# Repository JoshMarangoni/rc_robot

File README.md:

# rc_robot

## Project Motivation

NASA's Perseverance rover is a remote controllable rover designed to explore the surface of the Red Planet. The rover primarily uses an ultra-high frequency antenna to communicate with Earth. Data is relayed through Mars satellites back to Earth where engineers can monitor the robot's trajectory and speed.

Although my robot is not designed for Mars, it is designed to explore the outer reaches of my kitchen and living room while I am comfortably relaxing in my bedroom. Instead of orbitting satellites I use my WiFi network and communicate with my robot using http requests. This project is intended to emulate a remote controlled rover such as Perserverence, using my own circuit and software designs.

## Requirements

- Must be able to drive in any direction
- Programmed in C/C+
- Non-arduino based coding envrionment
- Battery powered
- Map "WASD" keys to driving direction

## Bonus features

- All electronics contained on one PCB
- Remote controlled using video feed
- Lag between key presses and robot response < 0.5 s

## Design 1 (MVP) - DONE

- ESP 32 microcontroller programmed in Arduino
- 2 wheels/motors in the rear (RWD)
- 1 wheel/motor in the front
- esp32CAM for video streaming
- Plexiglass chassis

## Design 2 (Feature Complete) - Done

- ESP32 programmed in Expressif IoT Development Framework
- PCB designed in KiCAD and fabricated by JLC PCB
- control terminal for WASD keys written in Python

### Planning (created after completing Design 1)
| Task                                         | Deadline |
|----------------------------------------------|----------|
| get 3D printer working | Nov.19 (Sat) |
| receive MOSFETs | Nov.19 (Sat) |
| get H-bridges working | Nov.20 (Sun) |
| test singular power source with capacitor | Nov.20 (Sun) |
| finish PCB design and send order for fab | Nov.27 (Sun) |
| make CAD drawing for chassis and 3D print | Dec.4  (Sun) |
| receive PCB | Dec.7  (Wed) |
| solder components on PCB and test | Dec.11 (Sun) |
| finish all software | Dec.18 (Sun) |

### Demo YouTube Videos

### Key Learnings
- even though a motor draws 0.2 A while running it can produce a stall current of 2+ A, causing the driver to underpower the arduino
  - meaured the 5V output of the Arduino and saw the voltage hang around 3 V sometimes dropping even lower as the motors change directions. I need to either put the motors on a separate power supply or use large capacitors to buffer voltage spikes
  - After doing some research I found out that the larger the current draw is from the battery, the lower the batteries output voltage will be due to the internal voltage drop. Batteries have an internal resistance, so the larger the current out of the battery, the larger the internal drop, and the lower the output voltage will be. Hypothesis, to solve this, use batteries with larger capacity, such as two 18650's in series, which have a combined 2800mAh capacity. Results: it worked!
- Got video streaming over Bluetooth by changing ArduCAM's serial prints to use SerialBT, then using a BT virtual COM port for the host app
- Tried combining all the camera source code, bluetooth serial, http webserver, and motor controls all in one program, but the program is too large for the ESP32. Further, I do not want the camera streaming software to be delayed by running motor controls and http server responses in the same control loop. I could use FreeRTOS to split up these tasks, but that seems overkill. There is no need to have all this code on one processor when I can buy an integrated esp32-CAM that I can dedicate to video streaming. Having the robot be controlled over WIFI is also superior to Bluetooth as it allows me to operate the vehicle compleletely remotely as long as I have the WIFI router's IP address and port forwarding setup.
- Do a beep test on a PCB before placing components
- DO NOT POWER UP PCB UNTIL YOU ARE SURE EVERYTHING IS CONNECTED PROPERLY
- BE VERY SURE you don't mix up power and ground, as reversing the polarity will surely fry your components
- If hand soldering a PCB, do it in stages, and test each module individually as you go

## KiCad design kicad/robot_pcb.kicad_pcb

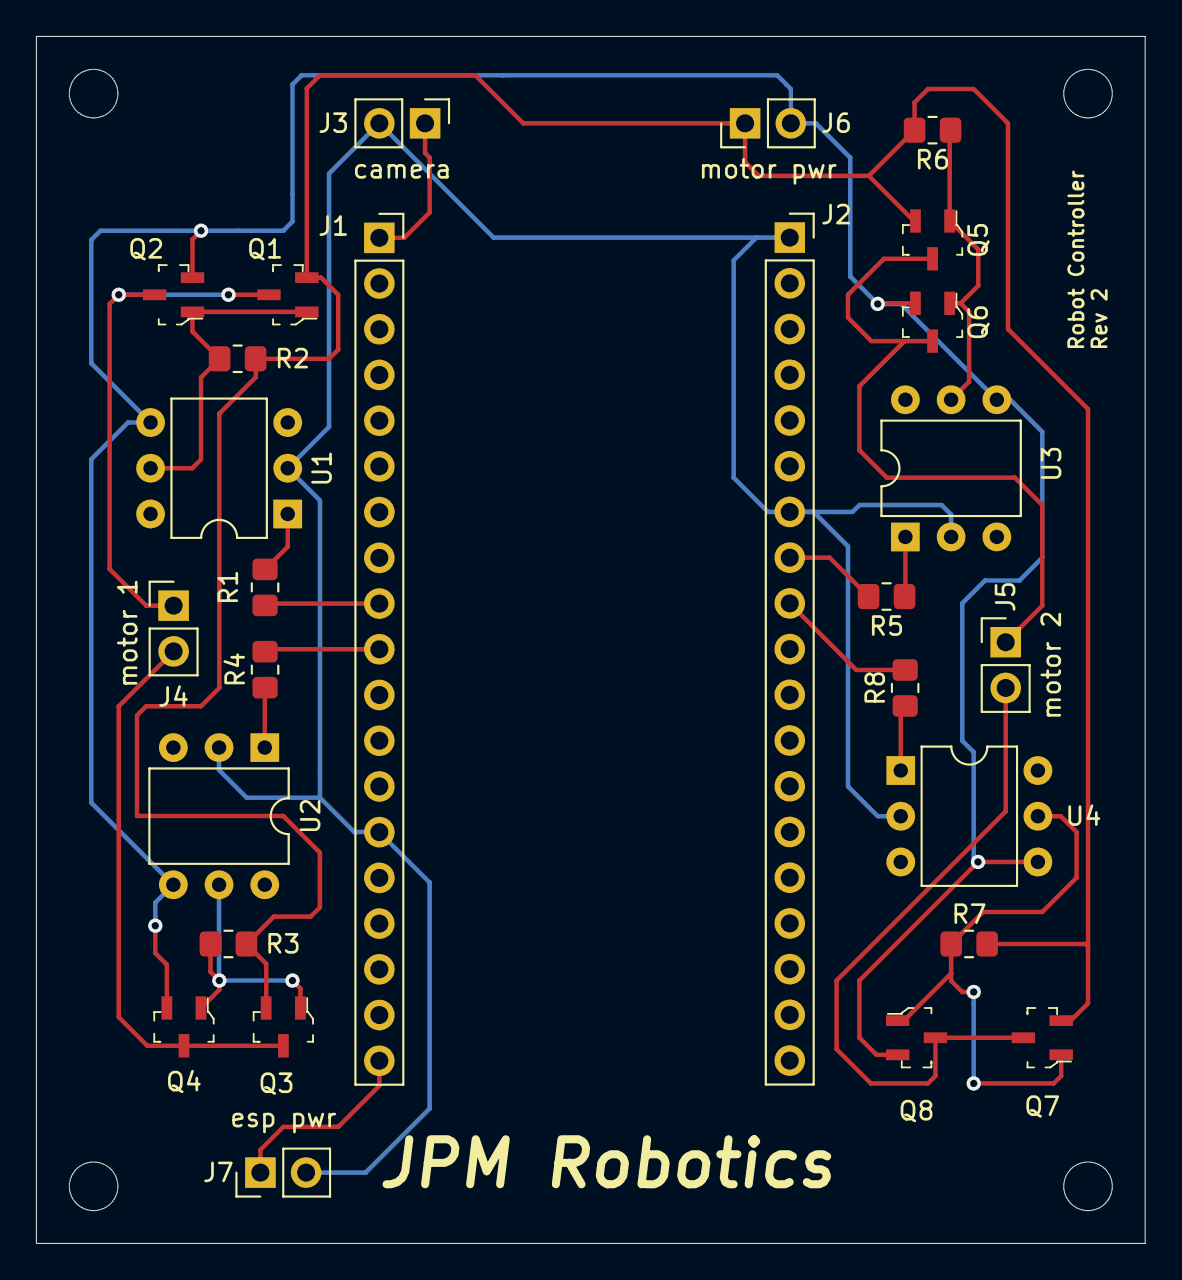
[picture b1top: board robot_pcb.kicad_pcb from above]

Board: 2 copper layers, 61.6 x 67.1 mm, 31 parts (0 on the bottom side), 21 nets.

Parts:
J1, J2: Conn_01x19_Female; PinSocket_1x19_P2.54mm_Vertical
J3: esp32 cam; PinHeader_1x02_P2.54mm_Vertical
J4: motor1; PinHeader_1x02_P2.54mm_Vertical
J5: motor2; PinHeader_1x02_P2.54mm_Vertical
J6: motor pwr; PinHeader_1x02_P2.54mm_Vertical
J7: esp32 pwr; PinHeader_1x02_P2.54mm_Vertical
Q1, Q3, Q5, Q7: AO3401A; SOT-23-3
Q2, Q4, Q6, Q8: IRLML6344TRPBF; SOT-23-3
R1, R4, R5, R8: 1k; R_0805_2012Metric_Pad1.20x1.40mm_HandSolder
R2, R3, R6, R7: 47k; R_0805_2012Metric_Pad1.20x1.40mm_HandSolder
REF1, REF2, REF3, REF4: MountingHole_2.7mm_M2.5
U1, U2, U3, U4: 4N25; DIP-6_W7.62mm

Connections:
/3.3V: J1.1, J3.1
/Gate1: Q1.1 (G), Q2.1 (G), R2.1, U1.5
/Gate2: Q3.1 (G), Q4.1 (G), R3.1, U2.5
/Gate3: Q5.1 (G), Q6.1 (G), R6.1, U3.5
/Gate4: Q7.1 (G), Q8.1 (G), R7.1, U4.5
/Vcc: J1.19, J7.1
/Vm: J6.1, Q1.2 (S), Q3.2 (S), Q5.2 (S), Q7.2 (S), R2.2, R3.2, R6.2, R7.2
ESP_GND: J1.14, J2.1, J2.7, J3.2, J7.2, U1.2, U2.2, U3.2, U4.2
M11: J1.9, R1.2
M12: J1.10, R4.2
M21: J2.8, R5.2
M22: J2.9, R8.2
MGND: J6.2, Q2.2 (S), Q4.2 (S), Q6.2 (S), Q8.2 (S), U1.4, U2.4, U3.4, U4.4
MO1: J4.1, Q1.3 (D), Q2.3 (D)
MO2: J4.2, Q3.3 (D), Q4.3 (D)
MO3: J5.1, Q5.3 (D), Q6.3 (D)
MO4: J5.2, Q7.3 (D), Q8.3 (D)
unnamed: R1.1, U1.1
unnamed: R4.1, U2.1
unnamed: R5.1, U3.1
unnamed: R8.1, U4.1

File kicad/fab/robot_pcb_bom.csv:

Comment,Designator,Package,Quantity,Designation,LCSC Part Number
2-pin male header,J7,PinHeader_1x02_P2.54mm_Vertical,1,esp32 pwr,
"pmos transistor (30V,4A)","Q3,Q1,Q7,Q5",SOT-23-3,4,AO3401A,C15127
19-pin female header,"J1,J2",PinSocket_1x19_P2.54mm_Vertical,2,Conn_01x19_Female,
"nmos transistor (30V, 5A)","Q4,Q6,Q8,Q2",SOT-23-3,4,IRLML6344TRPBF,C53550
2-pin male header,J3,PinHeader_1x02_P2.54mm_Vertical,1,esp32 cam,
1k smd (0805) resistor,"R5,R8,R1,R4",R_0805_2012Metric_Pad1.20x1.40mm_HandSolder,4,1k,
optoisolater,"U3,U1,U4,U2",DIP-6_W7.62mm,4,4N25,C115480
47k smd (0805) resistor,"R3,R6,R2,R7",R_0805_2012Metric_Pad1.20x1.40mm_HandSolder,4,47k,
2-pin male header,J6,PinHeader_1x02_P2.54mm_Vertical,1,motor pwr,
2-pin male header,J4,PinHeader_1x02_P2.54mm_Vertical,1,motor1,
2-pin male header,J5,PinHeader_1x02_P2.54mm_Vertical,1,motor2,

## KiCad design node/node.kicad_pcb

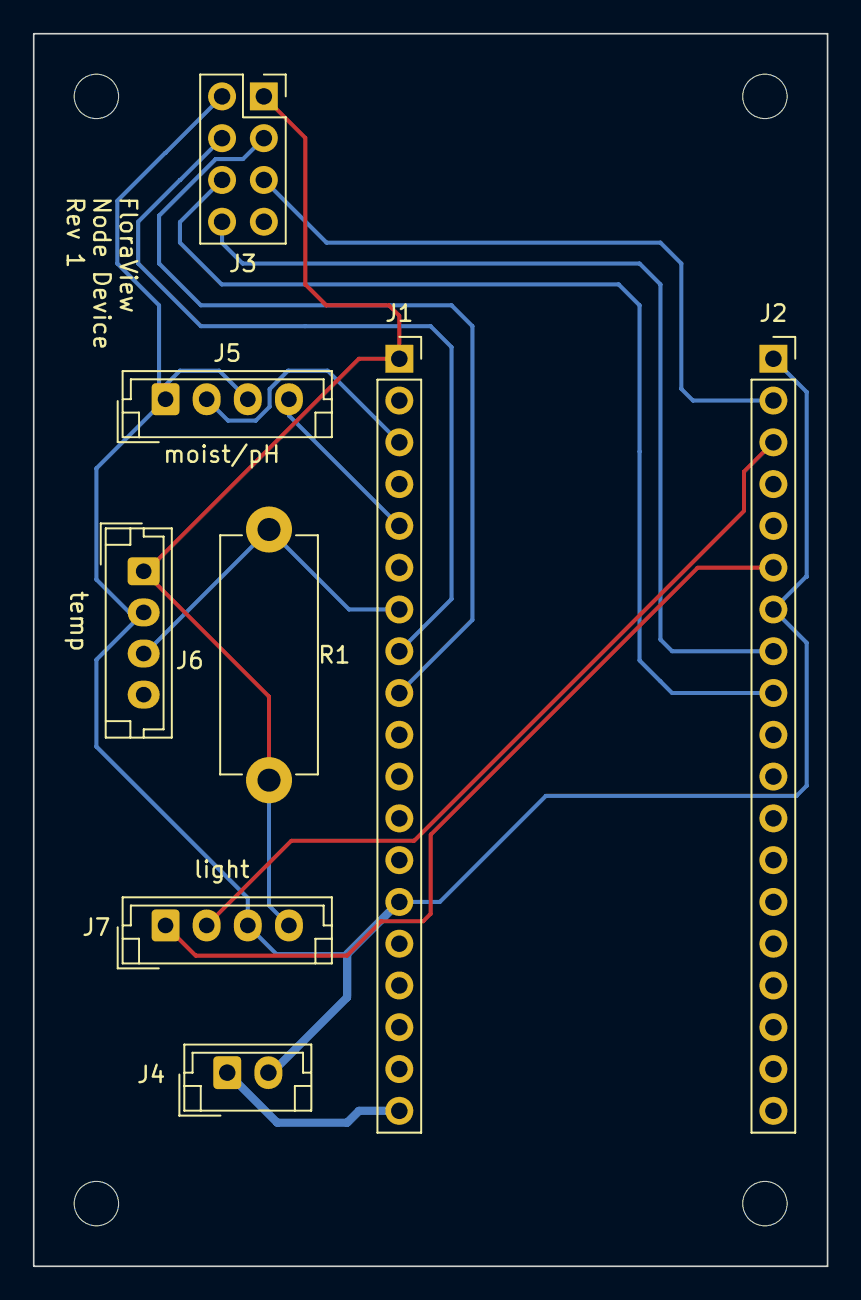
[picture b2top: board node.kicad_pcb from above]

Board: 2 copper layers, 48.3 x 74.9 mm, 12 parts (0 on the bottom side), 13 nets.

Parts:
J1, J2: Conn_01x19_Female; PinSocket_1x19_P2.54mm_Vertical
J3: Conn_02x04_Odd_Even; PinSocket_2x04_P2.54mm_Vertical
J4: Conn_01x02_Female; JST_EH_B2B-EH-A_1x02_P2.50mm_Vertical
J5, J6, J7: Conn_01x04_Female; JST_EH_B4B-EH-A_1x04_P2.50mm_Vertical
R1: 5k; R_Axial_DIN0614_L14.3mm_D5.7mm_P15.24mm_Horizontal
REF1, REF2, REF3, REF4: MountingHole_2.7mm_M2.5

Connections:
/3.3V: J1.1, J3.7, J6.1, J7.4, R1.2
GND: J1.14, J2.1, J2.7, J3.8, J4.2, J5.1, J5.3, J6.2, J7.3
unnamed: J1.3, J5.2
unnamed: J1.5, J5.4
unnamed: J1.7, J6.3, R1.1
unnamed: J1.8, J3.6
unnamed: J1.9, J3.5
unnamed: J1.19, J4.1
unnamed: J2.2, J3.3
unnamed: J2.3, J7.2
unnamed: J2.6, J7.1
unnamed: J2.8, J3.2
unnamed: J2.9, J3.4

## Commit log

2022-09-06 basic motor control
2022-09-10 update motor driver
2022-09-11 motor drive with esp32
2022-09-11 add HTTP LED control
2022-09-12 http motor control
2022-10-12 upload video streaming sketch
2022-10-12 print serial over Bluetooth
2022-10-24 upload test serial scripts
2022-10-27 save
2022-10-27 working
2022-11-01 init main
2022-11-02 add motor and web server code
2022-11-03 out of program storage space
2022-11-03 add notes
2022-11-07 upload esp32 cam code
2022-11-07 create new main
2022-11-07 add endpoint for turning left and right
2022-11-08 upload python robot controls
2022-11-08 sync get request controls working
2022-11-08 add all endpoints
2022-11-15 datasheets
2022-11-16 copy node pcb project
2022-11-16 make robot schematics
2022-11-16 add node for reference
2022-11-16 README planning
2022-11-16 formatting
2022-11-16 add markdown table
2022-11-19 single power source working!
2022-11-20 upload optoisolator datasheet
2022-11-21 h-bridge motor test
2022-11-22 pcb layout
2022-11-25 pcb design complete
2022-11-25 pcb done
2022-11-25 cleanup
2022-11-25 generate gerbers
2022-11-26 re-organize
2022-11-26 create chassis CAD
2022-11-26 add measurements kicad
2022-11-27 update stl
2022-11-27 backups
2022-11-27 upload fw readme
2022-11-27 move sketches to arduino folder
2022-11-27 upload arduino folder
2022-11-27 upload first kicad image
2022-11-27 create sample main esp idf
2022-11-27 upload .gitignore
2022-11-27 hello from main
2022-11-27 upload esp idf README
2022-11-27 blink LED
2022-11-28 add http server to main
2022-11-28 add LED toggle to http server
2022-11-28 create blink and hello endpoints
2022-11-28 create generic get handler
2022-11-28 add function stubs for motor controls
2022-11-28 implement motor drivers
2022-11-28 cleanup main
2022-11-30 update project readme
2022-11-30 update requirements
2022-12-04 pcb rev 2
2022-12-04 exclude kicad backups
2022-12-04 update datasheets
2022-12-04 sent out fab for rev2 pcb
2022-12-04 remove backups from remote
2022-12-04 upload images
2022-12-04 upload imges
2022-12-04 add measurements
2023-05-14 arduino control test both motors
2023-05-16 update motor pins
2023-05-19 update get request script
2023-05-19 full async terminal and async http
2023-05-19 nits
2023-07-16 upload link to YT video
2024-05-01 update motor controls
2024-05-01 upload pinout
2024-05-01 remove un-needed code
2024-05-02 clean up http get handler
2024-05-02 user_ctx for response data
2024-05-02 improve start_webserver()
2024-05-03 update control terminal
2024-05-08 add comment
